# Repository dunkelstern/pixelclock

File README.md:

# Pixel clock

This is an ornamental LED clock based on the standard SK6212 programmable
LED-Strips.

You will find a KiCAD schematic for an ESP32 module based PCB in the `/kicad`
folder.

To compile you will need Platform.io.

## Images

## Basic settings

For Hardware setup look into `/include/config.hpp` you can set up the following
things there:

1. `MY_NAME` is used as a MDNS Hostname as well as for MQTT topics if MQTT is enabled
2. `NEOPIXEL_IS_RGBW`, set this to 1 if you use Neopixel strips that have 4 color components (the 4. is usually White)
3. `NEOPIXEL_TYPE` see the documentation of [Neopixelbus]() for values you can use here...
4. `NEOPIXEL_PIN` the GPIO number where you connected the neopixel ring.

You have to configure the device by connecting to the AP it will open (`Pixelclock`, password is `pixelclock`) and open the website it provides at `<MY_NAME>.local`.

## TODO

- Standalone AP when no Wifi is configured
- Website that allows configuration
- JSON based API that will be used by the website
- Webserver to serve Website
- Add RTC support to PCB
- Add RTC support to code
- Documentation and pictures of finished project

## Done

- MQTT connection
- NTP update to automatically fetch time
- Saving of values to internal flash to persist settings across reboots
- Actual display of clock
- Home Assistant autoconfiguration
- Basic PCB layout
- 3D Printed parts to build clock
- 3D Printed electronics enclosure
- Topology configuration (if you have to hang the thing upside down, etc.)

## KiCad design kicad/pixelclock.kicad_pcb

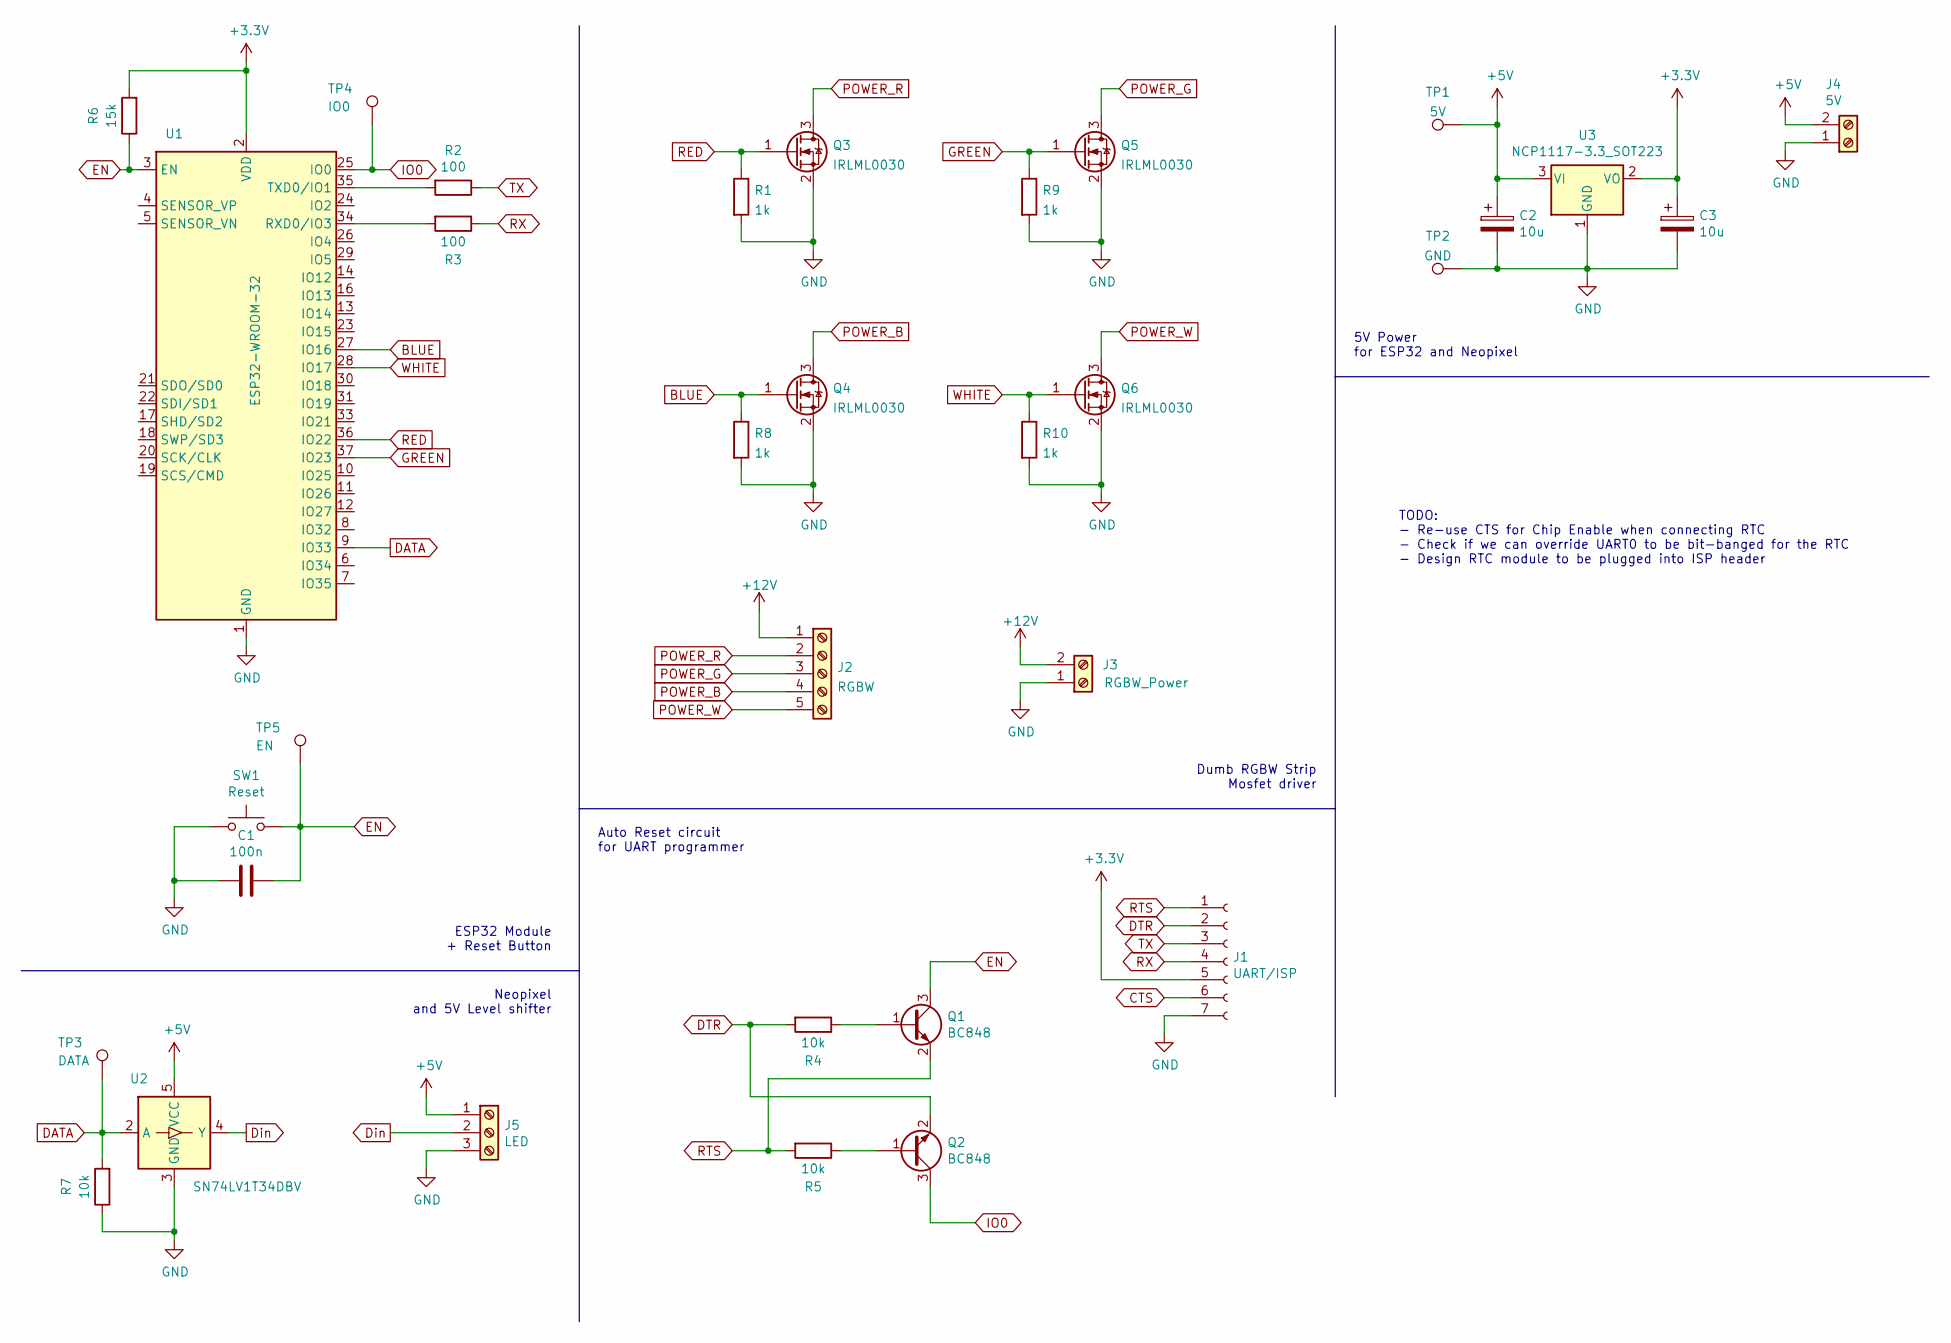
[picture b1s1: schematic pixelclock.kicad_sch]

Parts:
C1: 100n; C_0805_2012Metric_Pad1.18x1.45mm_HandSolder
C2, C3: 10u; CP_Elec_4x5.3
J1: UART/ISP; PinSocket_1x07_P2.54mm_Horizontal
J2: RGBW; TerminalBlock_Phoenix_PT-1,5-5-3.5-H_1x05_P3.50mm_Horizontal
J3: RGBW_Power; TerminalBlock_Phoenix_PT-1,5-2-3.5-H_1x02_P3.50mm_Horizontal
J4: 5V; TerminalBlock_Phoenix_PT-1,5-2-3.5-H_1x02_P3.50mm_Horizontal
J5: LED; TerminalBlock_Phoenix_PT-1,5-3-3.5-H_1x03_P3.50mm_Horizontal
Q1, Q2: BC848; SOT-23
Q3, Q4, Q5, Q6: IRLML0030; SOT-23
R1, R8, R9, R10: 1k; R_0805_2012Metric_Pad1.20x1.40mm_HandSolder
R2, R3: 100; R_0805_2012Metric_Pad1.20x1.40mm_HandSolder
R4, R5, R7: 10k; R_0805_2012Metric_Pad1.20x1.40mm_HandSolder
R6: 15k; R_0805_2012Metric_Pad1.20x1.40mm_HandSolder
SW1: Reset; SW_Push_1P1T_NO_6x6mm_H9.5mm
TP1: 5V; TestPoint_Pad_1.5x1.5mm
TP2: GND; TestPoint_Pad_1.5x1.5mm
TP3: DATA; TestPoint_Pad_1.5x1.5mm
TP4: IO0; TestPoint_Pad_1.5x1.5mm
TP5: EN; TestPoint_Pad_1.5x1.5mm
U1: ESP32-WROOM-32
U2: SN74LV1T34DBV; SOT-23-5
U3: NCP1117-3.3_SOT223; SOT-223-3_TabPin2

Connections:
+3V3: C3.1, J1.5, R6.2, U1.2 (VDD), U3.2 (VO)
+5V: C2.1, J4.2, J5.1, TP1.1, U2.5 (VCC), U3.3 (VI)
+12V: J2.1, J3.2
BLUE: Q4.1 (G), R8.1, U1.27 (IO16)
CTS: J1.6
DATA: R7.2, TP3.1, U1.9 (IO33), U2.2 (A)
DTR: J1.2, Q2.2 (E), R4.2
Din: J5.2, U2.4 (Y)
EN: C1.1, Q1.3 (C), R6.1, SW1.2, TP5.1, U1.3 (EN)
GND: C1.2, C2.2, C3.2, J1.7, J3.1, J4.1, J5.3, Q3.2 (S), Q4.2 (S), Q5.2 (S), Q6.2 (S), R1.2, R7.1, R8.2, R9.2, R10.2, SW1.1, TP2.1, U1.1 (GND), U1.15 (GND), U1.38 (GND), U1.39 (GND), U2.3 (GND), U3.1 (GND)
GREEN: Q5.1 (G), R9.1, U1.37 (IO23)
IO0: Q2.3 (C), TP4.1, U1.25 (IO0)
unnamed: Q1.1 (B), R4.1
unnamed: Q2.1 (B), R5.1
unnamed: R2.2, U1.35 (TXD0/IO1)
unnamed: R3.2, U1.34 (RXD0/IO3)
POWER_B: J2.4, Q4.3 (D)
POWER_G: J2.3, Q5.3 (D)
POWER_R: J2.2, Q3.3 (D)
POWER_W: J2.5, Q6.3 (D)
RED: Q3.1 (G), R1.1, U1.36 (IO22)
RTS: J1.1, Q1.2 (E), R5.2
RX: J1.4, R3.1
TX: J1.3, R2.1
WHITE: Q6.1 (G), R10.1, U1.28 (IO17)

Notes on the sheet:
ESP32 Module + Reset Button
Auto Reset circuit for UART programmer
5V Power for ESP32 and Neopixel
Dumb RGBW Strip Mosfet driver
Neopixel and 5V Level shifter
TODO: - Re-use CTS for Chip Enable when connecting RTC - Check if we can override UART0 to be bit-banged for the RTC - Design RTC module to be plugged into ISP header

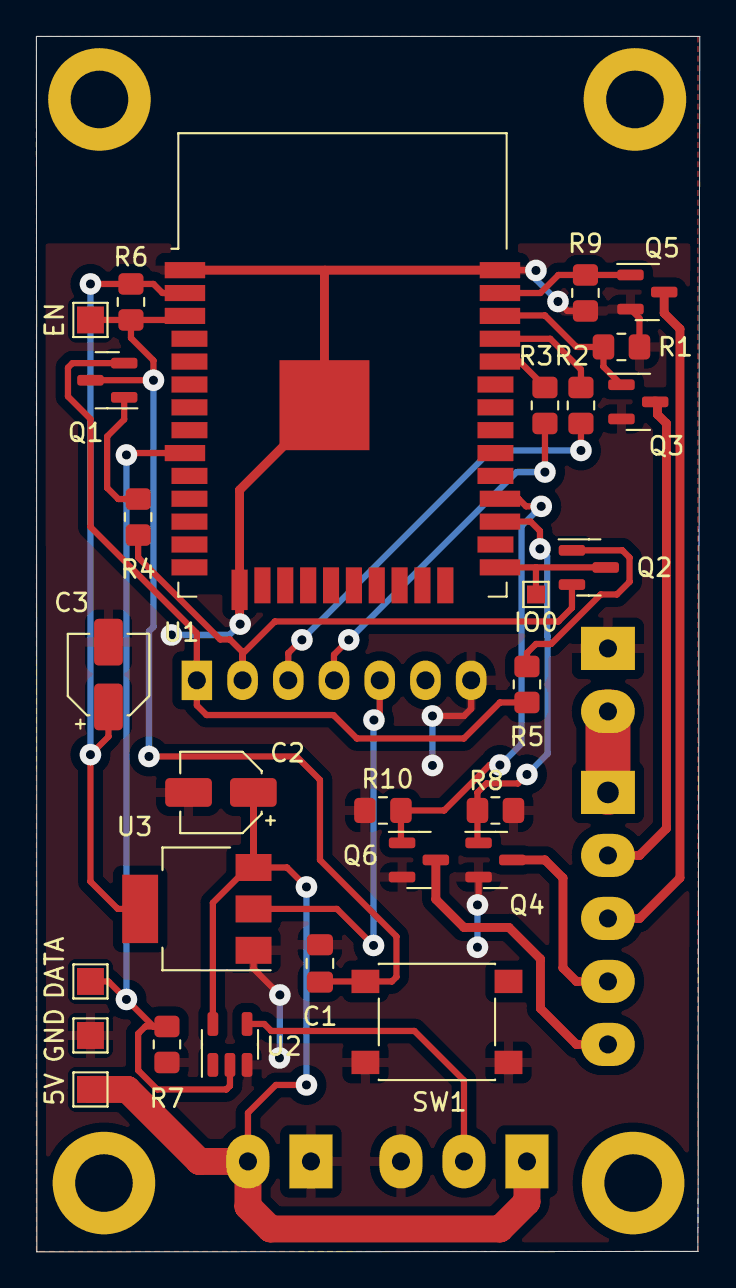
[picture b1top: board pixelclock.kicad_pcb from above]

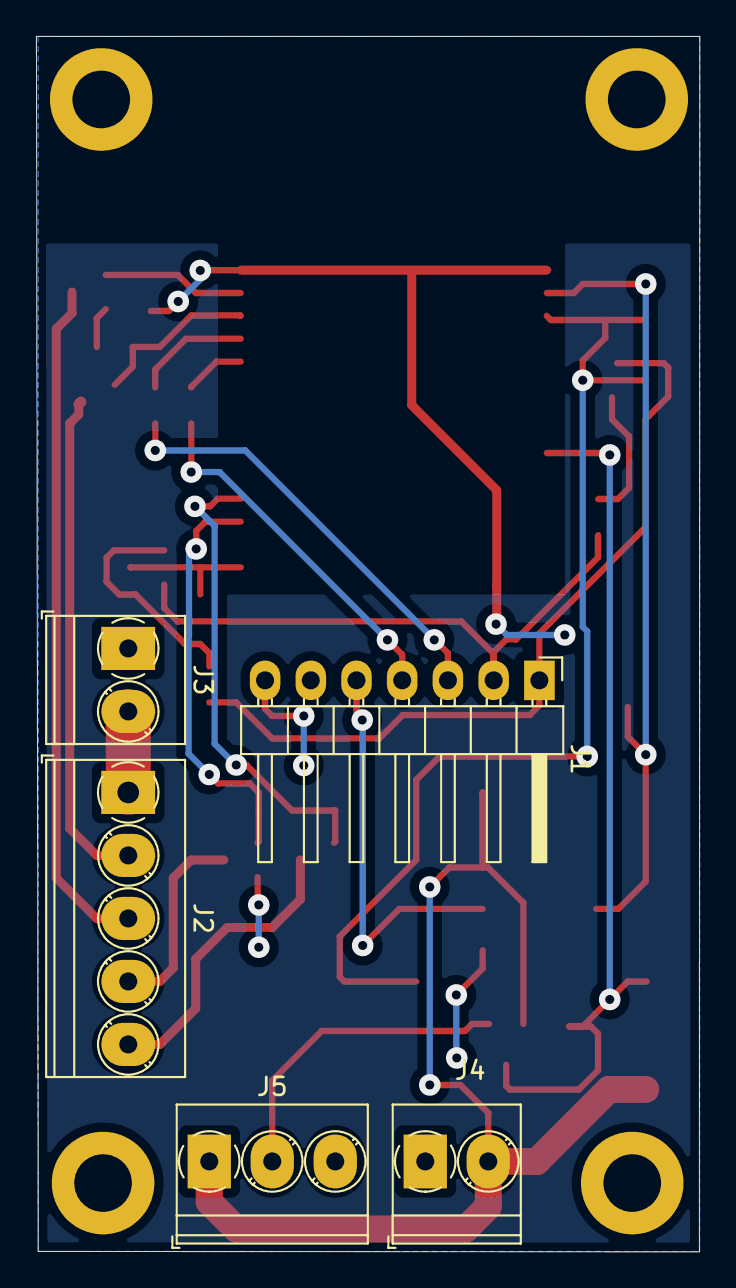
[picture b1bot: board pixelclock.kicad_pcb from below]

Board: 2 copper layers, 36.8 x 67.5 mm, 37 parts (5 on the bottom side), 24 nets.

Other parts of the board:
M1: MountingHole_3.2mm_M3_ISO7380_Pad
MH2, MH3, MH4: MountingHole_3.2mm_M3_ISO7380_Pad

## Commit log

2022-01-13 Platform.io setup
2022-01-13 Kicad PCB files
2022-01-13 Arduino based ESP32 code
2022-01-13 Add STL files for 3D Printing
2022-01-13 Add Pictures and Schematic PDF
2022-01-13 Update to KiCad 6
2022-01-13 Remove unneeded stuff
2022-01-18 Update pixelclock board to support additional RGBW LED strip (dumb single color LED strip)
2022-01-18 Add software support for LED Strip driver circuitry
2022-01-18 Workaround for Bug in ESP Libs: Disable Wifi powersaving
